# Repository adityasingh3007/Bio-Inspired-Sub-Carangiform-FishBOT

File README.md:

# Bio-inspired-sub-carangiform-fishbot-2019

# Abstract:

Researches about underwater propulsion mainly illustrate the use of propellers or thrusters to propel a robot in an underwater environment whereas most of the aquatic animals change their body shape in order to navigate.The shape-change generating propulsion force makes them move forward or backward effectively.The underwater fish robot is a kind of bionic robot which changes its body shape to navigate in underwater environment.The aim of the project is to understand the dynamics of underwater robots in general and the effect of lift, drag and hydrodynamic coefficients on them and to simulate, validate and develop a fish bot robot which is robust enough to carry out underwater exploratory tasks.

## Team:

  • Aditya Kumar Singh [https://github.com/adityasingh3007]

  • Bhavy Shah [https://github.com/Ragnhide]

## Mentors:

  • Rucmenya Bessariya 

  • Saail Narvekar 

  • Lohit Penubaku 

# Repository Organized.

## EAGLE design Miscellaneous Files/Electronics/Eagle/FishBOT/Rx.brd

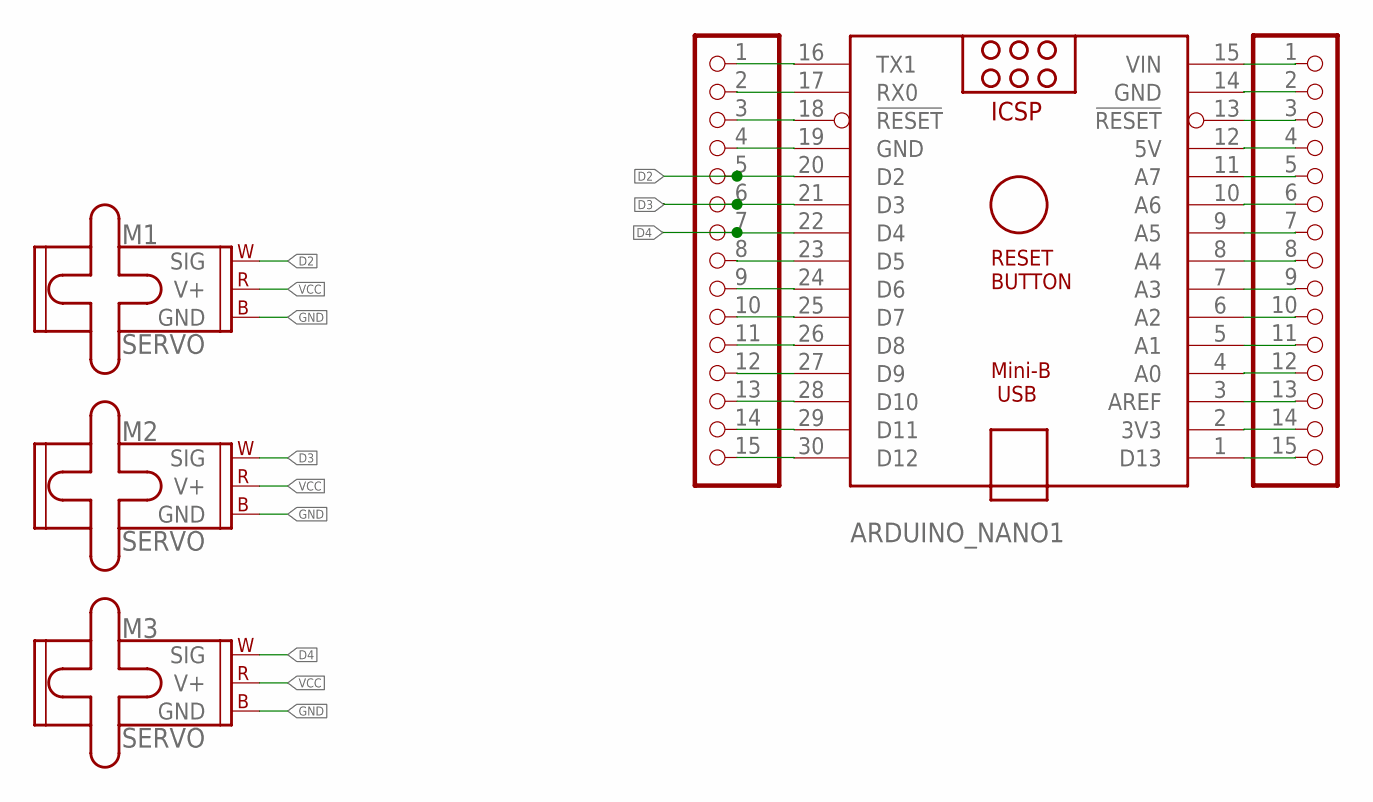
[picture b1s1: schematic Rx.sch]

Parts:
ARDUINO_NANO1: ARDUINO_NANO
JP1, JP2: PINHD-1X15-CB; 1X15-CB
M1, M2, M3: SERVO; 1X03

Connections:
D2: ARDUINO_NANO1.20 (D2), JP2.5, M1.1 (SIG)
D3: ARDUINO_NANO1.21 (D3), JP2.6, M2.1 (SIG)
D4: ARDUINO_NANO1.22 (D4), JP2.7, M3.1 (SIG)
GND: M1.3 (GND), M2.3 (GND), M3.3 (GND)
unnamed: ARDUINO_NANO1.16 (TX1), JP2.1
unnamed: ARDUINO_NANO1.17 (RX0), JP2.2
unnamed: ARDUINO_NANO1.18 (!RESET), JP2.3
unnamed: ARDUINO_NANO1.19 (GND), JP2.4
unnamed: ARDUINO_NANO1.23 (D5), JP2.8
unnamed: ARDUINO_NANO1.24 (D6), JP2.9
unnamed: ARDUINO_NANO1.25 (D7), JP2.10
unnamed: ARDUINO_NANO1.26 (D8), JP2.11
unnamed: ARDUINO_NANO1.27 (D9), JP2.12
unnamed: ARDUINO_NANO1.28 (D10), JP2.13
unnamed: ARDUINO_NANO1.29 (D11), JP2.14
unnamed: ARDUINO_NANO1.30 (D12), JP2.15
unnamed: ARDUINO_NANO1.15 (VIN), JP1.1
unnamed: ARDUINO_NANO1.14 (GND), JP1.2
unnamed: ARDUINO_NANO1.13 (!RESET), JP1.3
unnamed: ARDUINO_NANO1.12 (5V), JP1.4
unnamed: ARDUINO_NANO1.11 (A7), JP1.5
unnamed: ARDUINO_NANO1.10 (A6), JP1.6
unnamed: ARDUINO_NANO1.9 (A5), JP1.7
unnamed: ARDUINO_NANO1.8 (A4), JP1.8
unnamed: ARDUINO_NANO1.7 (A3), JP1.9
unnamed: ARDUINO_NANO1.6 (A2), JP1.10
unnamed: ARDUINO_NANO1.5 (A1), JP1.11
unnamed: ARDUINO_NANO1.4 (A0), JP1.12
unnamed: ARDUINO_NANO1.3 (AREF), JP1.13
unnamed: ARDUINO_NANO1.2 (3V3), JP1.14
unnamed: ARDUINO_NANO1.1 (D13), JP1.15
VCC: M1.2 (V+), M2.2 (V+), M3.2 (V+)

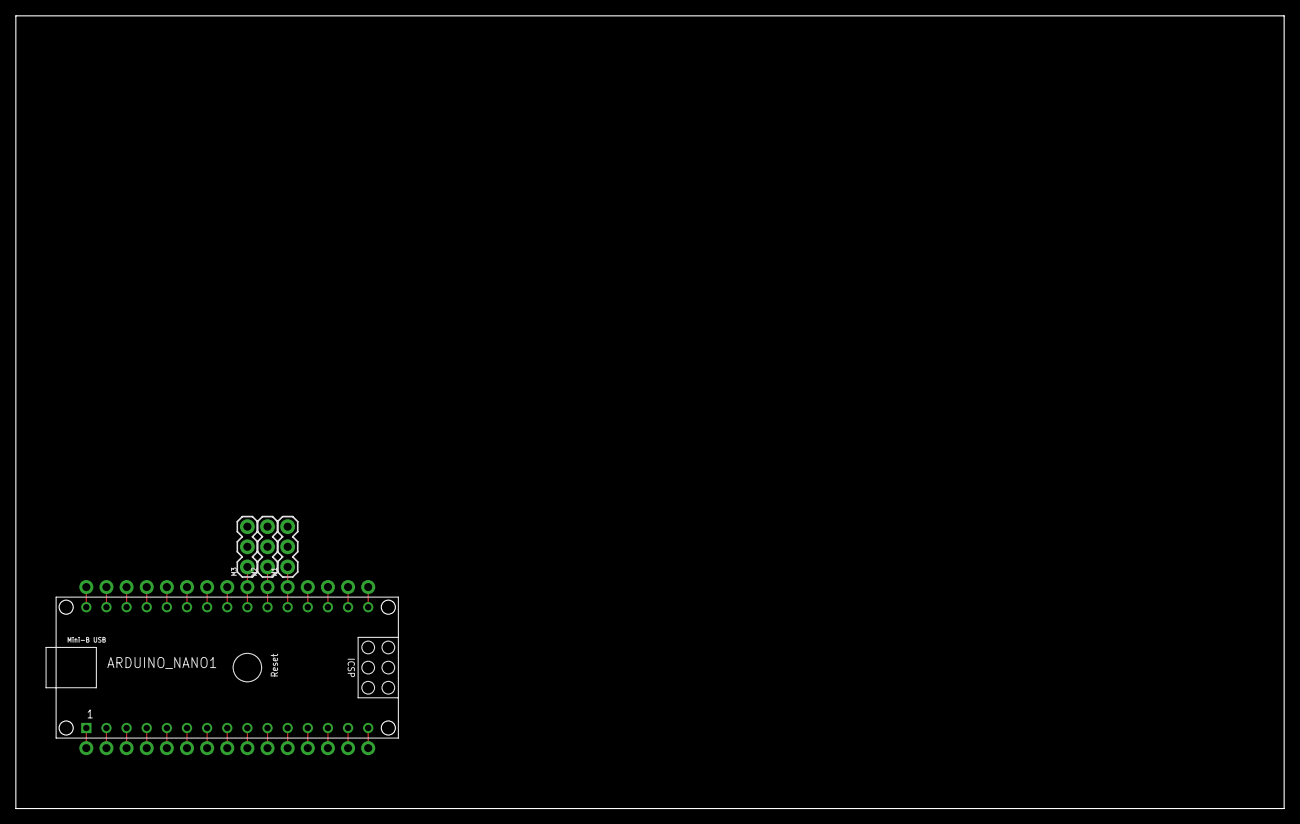
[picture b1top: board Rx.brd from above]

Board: 2 copper layers, 160.0 x 100.0 mm, 6 parts (1 on the bottom side), 32 nets.

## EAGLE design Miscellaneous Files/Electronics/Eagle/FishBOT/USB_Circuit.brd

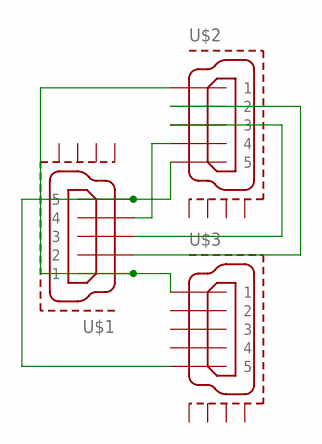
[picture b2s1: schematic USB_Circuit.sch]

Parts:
U$1, U$2, U$3: MICRO-USB-RECEPTACLE47589-0001; 47589-0001

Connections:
unnamed: U$1.5, U$2.5, U$3.5
unnamed: U$1.3, U$2.3
unnamed: U$1.2, U$2.2
unnamed: U$1.4, U$2.4
unnamed: U$1.1, U$2.1, U$3.1

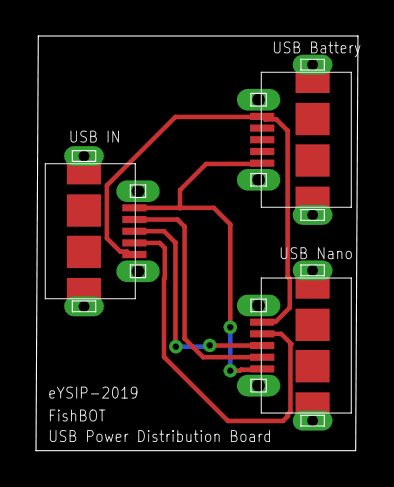
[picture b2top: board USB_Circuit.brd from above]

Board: 2 copper layers, 17.9 x 23.0 mm, 3 parts (0 on the bottom side), 5 nets.

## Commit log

2019-12-10 Final Codes added
2019-12-10 Poster added
2019-12-10 Solidworks files added
2019-12-10 Misc files added: :
2019-12-10 Images added
2019-12-10 Report added
2019-12-10 Readme updated. Final commit

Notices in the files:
parts and their libraries:
SparkFun-Electromechanical: Licensing: Creative Commons ShareAlike 4.0 International - https://creativecommons.org/licenses/by-sa/4.0
Micro_USB: (C) 2014 Tomasz Boleslaw CEDRO, cederom@tlen.pl, http://www.tomek.cedro.info.
